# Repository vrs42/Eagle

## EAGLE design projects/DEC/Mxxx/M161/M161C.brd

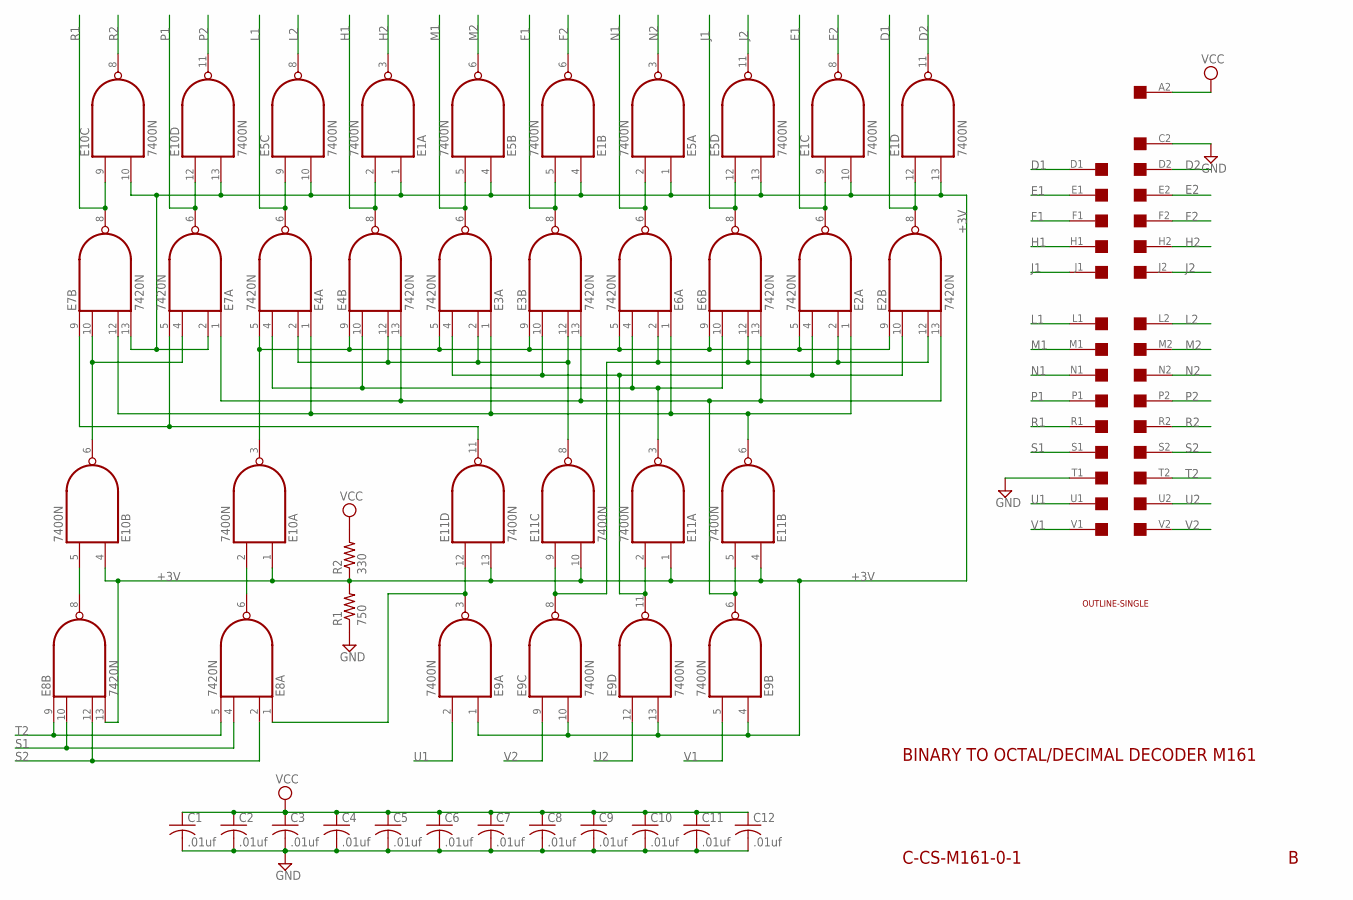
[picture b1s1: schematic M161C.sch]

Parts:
C1, C2, C3, C4, C5, C6, C7, C8, C9, C10, C11, C12: .01uf; C050-025X075
E1, E5, E9, E10, E11: 7400N; DIL14
E2, E3, E4, E6, E7, E8: 7420N; DIL14
R1: 750; 0207/10
R2: 330; 0207/10
U$1: OUTLINE-SINGLE; SINGLE
U$4: SINGLE; EDGE-CON2

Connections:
+3V: E1.1 (I0), E1.4 (I0), E1.10 (I1), E1.13 (I1), E5.1 (I0), E5.4 (I0), E5.10 (I1), E5.13 (I1), E7.2 (I1), E7.13 (I3), E8.13 (I3), E9.1 (I0), E9.4 (I0), E9.10 (I1), E9.13 (I1), E10.1 (I0), E10.4 (I0), E10.10 (I1), E10.13 (I1), E11.1 (I0), E11.4 (I0), E11.10 (I1), E11.13 (I1), R1.2, R2.1
D1: E1.12 (I0), E2.8 (O), U$4.D1
D2: E1.11 (O), U$4.D2
E1: E1.9 (I0), E2.6 (O), U$4.E1
E2: E1.8 (O), U$4.E2
F1: E1.5 (I1), E3.8 (O), U$4.F1
F2: E1.6 (O), U$4.F2
GND: C1.2, C2.2, C3.2, C4.2, C5.2, C6.2, C7.2, C8.2, C9.2, C10.2, C11.2, C12.2, E1.7 (GND), E2.7 (GND), E3.7 (GND), E4.7 (GND), E5.7 (GND), E6.7 (GND), E7.7 (GND), E8.7 (GND), E9.7 (GND), E10.7 (GND), E11.7 (GND), R1.1, U$4.C2, U$4.T1
H1: E1.2 (I1), E4.8 (O), U$4.H1
H2: E1.3 (O), U$4.H2
J1: E5.12 (I0), E6.8 (O), U$4.J1
J2: E5.11 (O), U$4.J2
L1: E4.6 (O), E5.9 (I0), U$4.L1
L2: E5.8 (O), U$4.L2
M1: E3.6 (O), E5.5 (I1), U$4.M1
M2: E5.6 (O), U$4.M2
N1: E5.2 (I1), E6.6 (O), U$4.N1
N2: E5.3 (O), U$4.N2
unnamed: E8.8 (O), E10.5 (I1)
unnamed: E7.4 (I2), E7.10 (I1), E10.6 (O)
unnamed: E2.5 (I3), E2.9 (I0), E3.5 (I3), E3.9 (I0), E4.5 (I3), E4.9 (I0), E6.5 (I3), E6.9 (I0), E10.3 (O)
unnamed: E8.6 (O), E10.2 (I1)
unnamed: E8.1 (I0), E9.3 (O), E11.12 (I0)
unnamed: E2.2 (I1), E2.12 (I2), E6.2 (I1), E6.12 (I2), E9.8 (O), E11.9 (I0)
unnamed: E2.4 (I2), E2.10 (I1), E3.4 (I2), E3.10 (I1), E9.11 (O), E11.2 (I1)
unnamed: E2.13 (I3), E3.13 (I3), E4.13 (I3), E6.13 (I3), E7.1 (I0), E9.6 (O), E11.5 (I1)
unnamed: E3.2 (I1), E3.12 (I2), E4.2 (I1), E4.12 (I2), E11.8 (O)
unnamed: E7.5 (I3), E7.9 (I0), E11.11 (O)
unnamed: E4.4 (I2), E4.10 (I1), E6.4 (I2), E6.10 (I1), E11.3 (O)
unnamed: E2.1 (I0), E3.1 (I0), E4.1 (I0), E6.1 (I0), E7.12 (I2), E11.6 (O)
P1: E7.6 (O), E10.12 (I0), U$4.P1
P2: E10.11 (O), U$4.P2
R1: E7.8 (O), E10.9 (I0), U$4.R1
R2: E10.8 (O), U$4.R2
S1: E8.4 (I2), E8.10 (I1), U$4.S1
S2: E8.2 (I1), E8.12 (I2), U$4.S2
T2: E8.5 (I3), E8.9 (I0), U$4.T2
U1: E9.2 (I1), U$4.U1
U2: E9.12 (I0), U$4.U2
V1: E9.5 (I1), U$4.V1
V2: E9.9 (I0), U$4.V2
VCC: C1.1, C2.1, C3.1, C4.1, C5.1, C6.1, C7.1, C8.1, C9.1, C10.1, C11.1, C12.1, E1.14 (VCC), E2.14 (VCC), E3.14 (VCC), E4.14 (VCC), E5.14 (VCC), E6.14 (VCC), E7.14 (VCC), E8.14 (VCC), E9.14 (VCC), E10.14 (VCC), E11.14 (VCC), R2.2, U$4.A2

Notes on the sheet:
BINARY TO OCTAL/DECIMAL DECODER M161
C-CS-M161-0-1

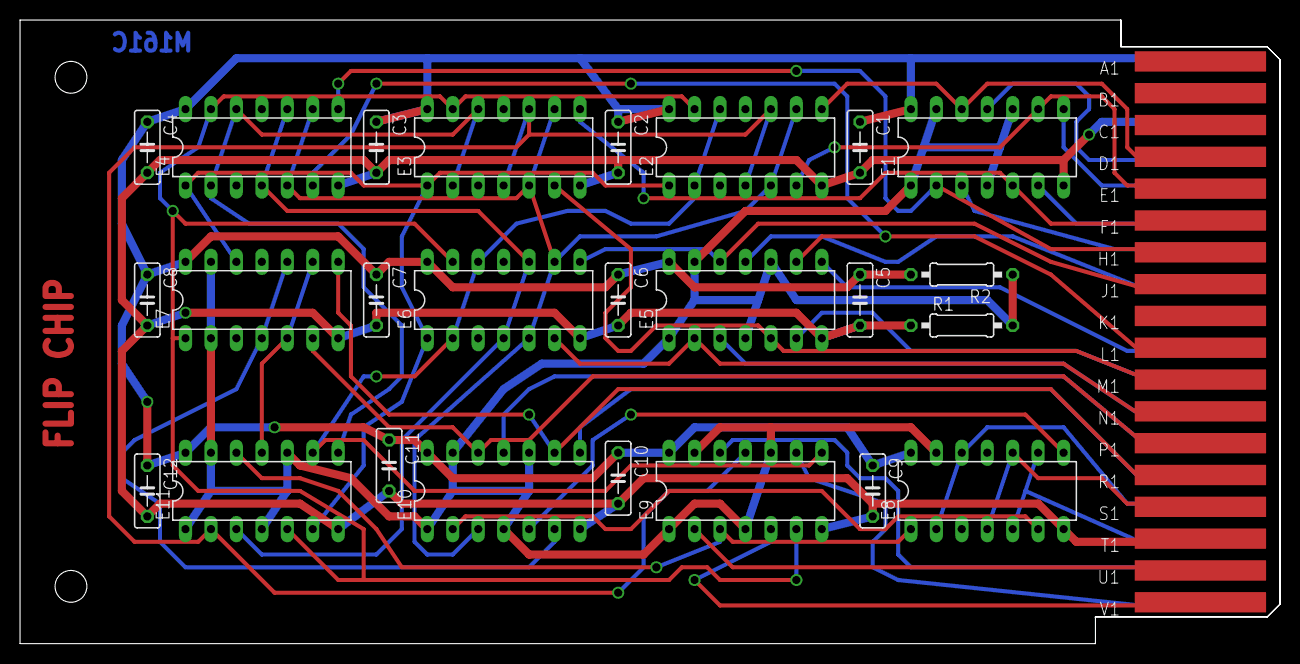
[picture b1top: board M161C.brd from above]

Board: 2 copper layers, 125.7 x 62.2 mm, 28 parts (0 on the bottom side), 42 nets.

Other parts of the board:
U$2: FLIPCHIP

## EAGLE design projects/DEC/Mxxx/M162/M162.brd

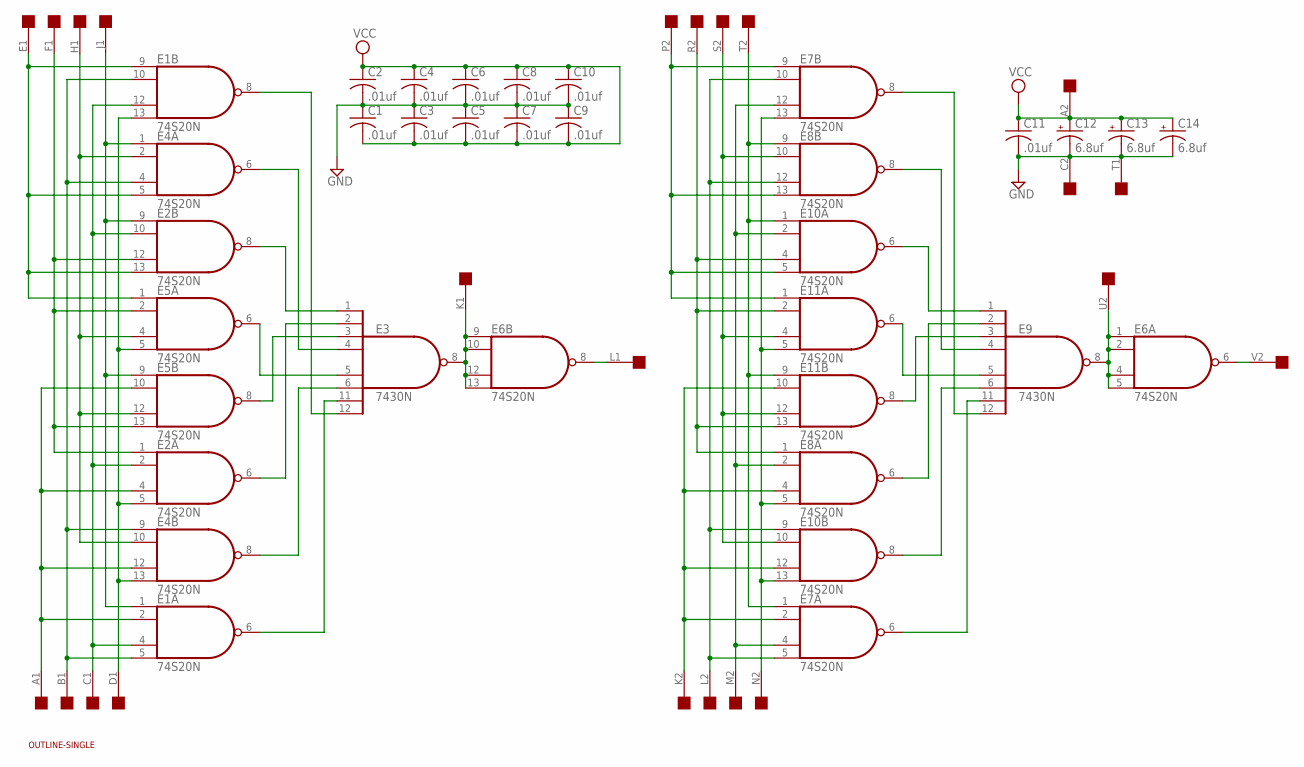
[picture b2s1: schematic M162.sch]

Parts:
C1, C2, C3, C4, C5, C6, C7, C8, C9, C10, C11: .01uf; C050-025X075
C12, C13, C14: 6.8uf; E22-6
E1, E2, E4, E5, E6, E7, E8, E10, E11: 74S20N; DIL14
E3, E9: 7430N; DIL14
U$1: OUTLINE-SINGLE; SINGLE
U$2: EDGE-2CONNECTOR; EDGE-CON2

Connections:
GND: C1.1, C2.2, C3.1, C4.2, C5.1, C6.2, C7.1, C8.2, C9.1, C10.2, C11.2, C12.-, C13.-, C14.-, E1.7 (GND), E2.7 (GND), E3.7 (GND), E4.7 (GND), E5.7 (GND), E6.7 (GND), E7.7 (GND), E8.7 (GND), E9.7 (GND), E10.7 (GND), E11.7 (GND), U$2.C2, U$2.T1
unnamed: E1.2 (I1), E2.4 (I2), E4.12 (I2), E5.10 (I1), U$2.A1
unnamed: E1.13 (I3), E2.5 (I3), E4.13 (I3), E5.5 (I3), U$2.D1
unnamed: E1.1 (I0), E2.9 (I0), E4.1 (I0), E5.9 (I0), U$2.J1
unnamed: E4.2 (I1), E4.10 (I1), E5.4 (I2), E5.12 (I2), U$2.H1
unnamed: E1.4 (I2), E1.12 (I2), E2.2 (I1), E2.10 (I1), U$2.C1
unnamed: E1.5 (I3), E1.10 (I1), E4.4 (I2), E4.9 (I0), U$2.B1
unnamed: E2.1 (I0), E2.12 (I2), E5.2 (I1), E5.13 (I3), U$2.F1
unnamed: E1.9 (I0), E2.13 (I3), E4.5 (I3), E5.1 (I0), U$2.E1
unnamed: E1.8 (O), E3.12 (I7)
unnamed: E3.4 (I3), E4.6 (O)
unnamed: E2.8 (O), E3.1 (I0)
unnamed: E3.5 (I4), E5.6 (O)
unnamed: E3.3 (I2), E5.8 (O)
unnamed: E2.6 (O), E3.2 (I1)
unnamed: E1.6 (O), E3.11 (I6)
unnamed: E3.6 (I5), E4.8 (O)
unnamed: E3.8 (O), E6.9 (I0), E6.10 (I1), E6.12 (I2), E6.13 (I3), U$2.K1
unnamed: E7.2 (I1), E8.4 (I2), E10.12 (I2), E11.10 (I1), U$2.K2
unnamed: E7.13 (I3), E8.5 (I3), E10.13 (I3), E11.5 (I3), U$2.N2
unnamed: E7.1 (I0), E8.9 (I0), E10.1 (I0), E11.9 (I0), U$2.T2
unnamed: E8.10 (I1), E10.10 (I1), E11.4 (I2), E11.12 (I2), U$2.S2
unnamed: E7.4 (I2), E7.12 (I2), E8.2 (I1), E10.2 (I1), U$2.M2
unnamed: E7.5 (I3), E7.10 (I1), E8.12 (I2), E10.9 (I0), U$2.L2
unnamed: E8.1 (I0), E10.4 (I2), E11.2 (I1), E11.13 (I3), U$2.R2
unnamed: E7.9 (I0), E8.13 (I3), E10.5 (I3), E11.1 (I0), U$2.P2
unnamed: E7.8 (O), E9.12 (I7)
unnamed: E8.8 (O), E9.4 (I3)
unnamed: E9.1 (I0), E10.6 (O)
unnamed: E9.5 (I4), E11.6 (O)
unnamed: E9.3 (I2), E11.8 (O)
unnamed: E8.6 (O), E9.2 (I1)
unnamed: E7.6 (O), E9.11 (I6)
unnamed: E9.6 (I5), E10.8 (O)
unnamed: E6.1 (I0), E6.2 (I1), E6.4 (I2), E6.5 (I3), E9.8 (O), U$2.U2
unnamed: E6.6 (O), U$2.V2
unnamed: E6.8 (O), U$2.L1
VCC: C1.2, C2.1, C3.2, C4.1, C5.2, C6.1, C7.2, C8.1, C9.2, C10.1, C11.1, C12.+, C13.+, C14.+, E1.14 (VCC), E2.14 (VCC), E3.14 (VCC), E4.14 (VCC), E5.14 (VCC), E6.14 (VCC), E7.14 (VCC), E8.14 (VCC), E9.14 (VCC), E10.14 (VCC), E11.14 (VCC), U$2.A2

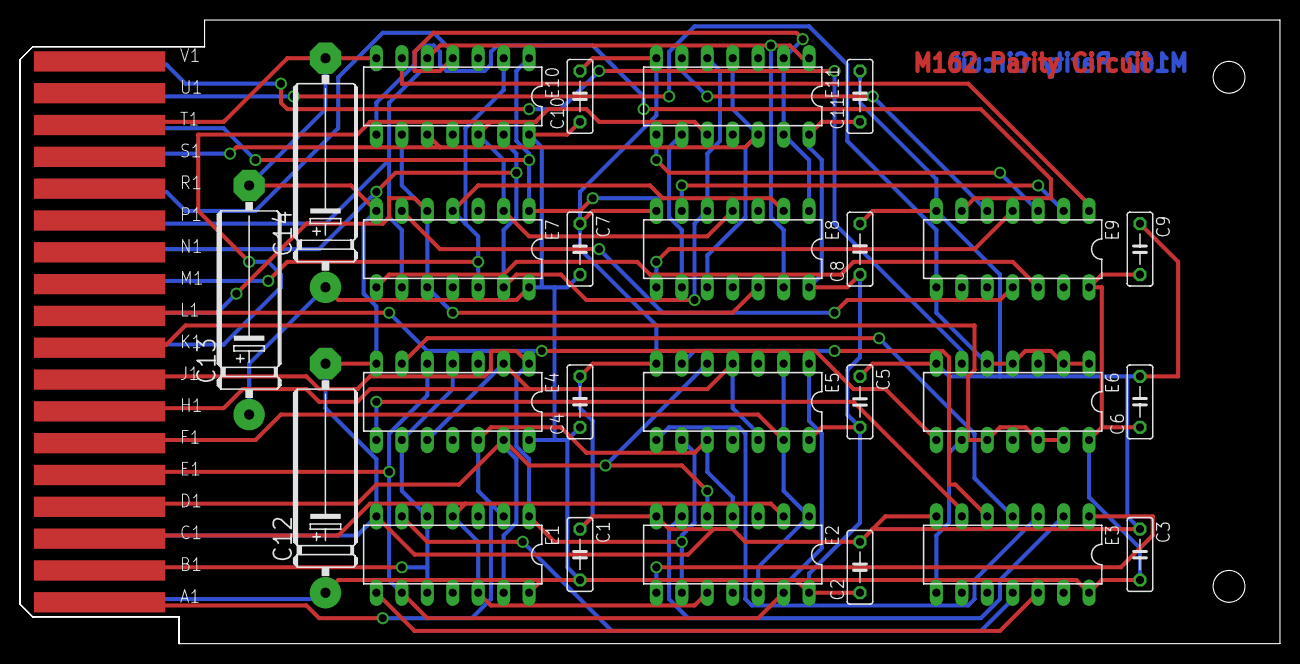
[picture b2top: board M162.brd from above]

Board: 2 copper layers, 125.7 x 62.2 mm, 27 parts (0 on the bottom side), 38 nets.

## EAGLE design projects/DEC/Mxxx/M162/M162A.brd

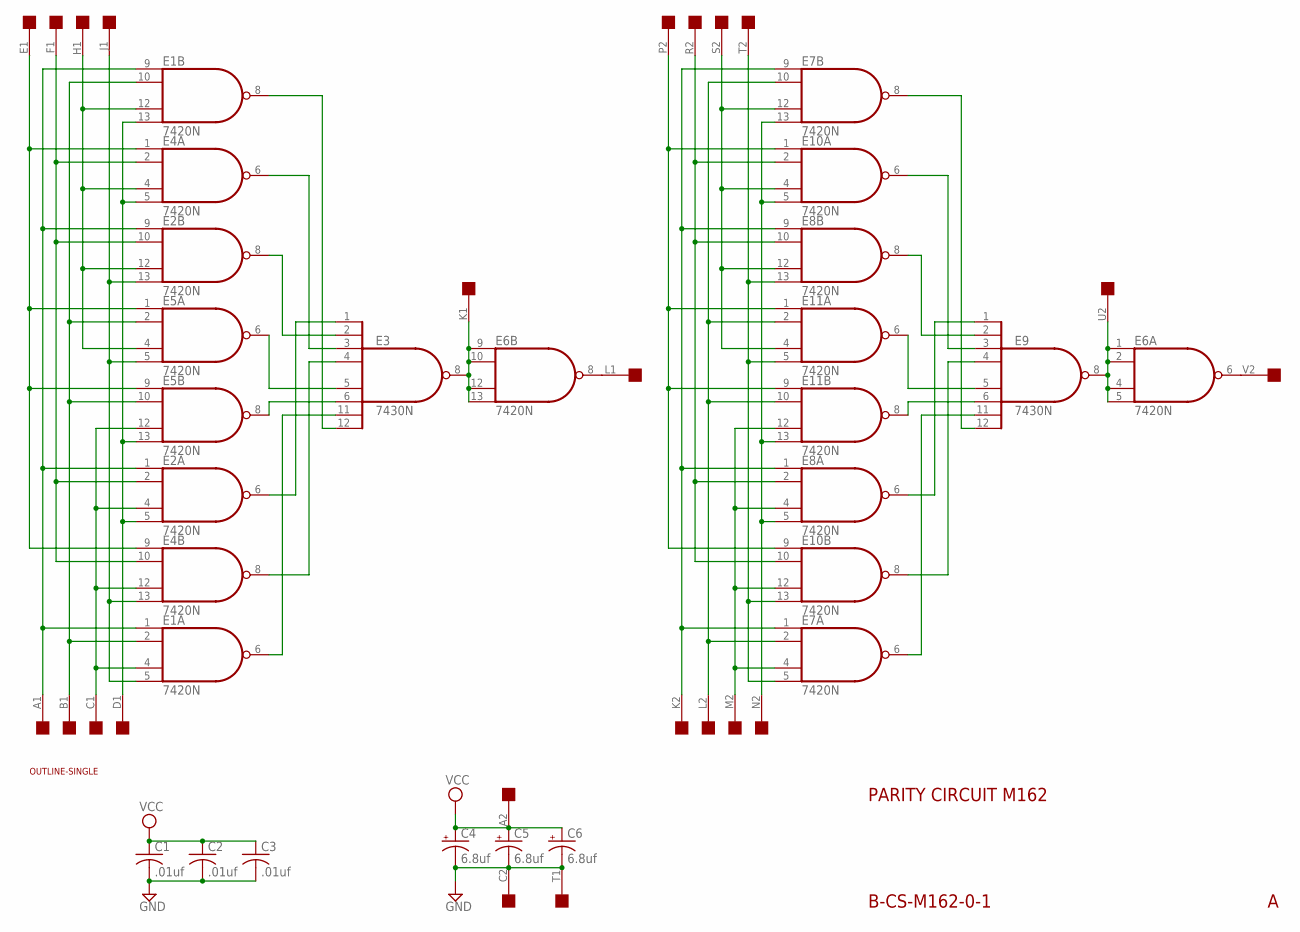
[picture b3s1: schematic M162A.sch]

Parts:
C1, C2, C3: .01uf; C075-032X103
C4, C5, C6: 6.8uf; E15-5
E1, E2, E4, E5, E6, E7, E8, E10, E11: 7420N; DIL14
E3, E9: 7430N; DIL14
U$1: OUTLINE-SINGLE; SINGLE
U$2: EDGE-2CONNECTOR; EDGE-CON2

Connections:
GND: C1.2, C2.2, C3.2, C4.-, C5.-, C6.-, E1.7 (GND), E2.7 (GND), E3.7 (GND), E4.7 (GND), E5.7 (GND), E6.7 (GND), E7.7 (GND), E8.7 (GND), E9.7 (GND), E10.7 (GND), E11.7 (GND), U$2.C2, U$2.T1
unnamed: E1.4 (I2), E2.4 (I2), E4.12 (I2), E5.12 (I2), U$2.C1
unnamed: E1.13 (I3), E2.5 (I3), E4.5 (I3), E5.13 (I3), U$2.D1
unnamed: E3.4 (I3), E4.8 (O)
unnamed: E1.12 (I2), E2.12 (I2), E4.4 (I2), E5.4 (I2), U$2.H1
unnamed: E2.2 (I1), E2.10 (I1), E4.2 (I1), E4.10 (I1), U$2.F1
unnamed: E1.2 (I1), E1.10 (I1), E5.2 (I1), E5.10 (I1), U$2.B1
unnamed: E7.12 (I2), E8.12 (I2), E10.4 (I2), E11.4 (I2), U$2.S2
unnamed: E1.1 (I0), E1.9 (I0), E2.1 (I0), E2.9 (I0), U$2.A1
unnamed: E1.8 (O), E3.12 (I7)
unnamed: E3.3 (I2), E4.6 (O)
unnamed: E7.6 (O), E9.11 (I6)
unnamed: E3.5 (I4), E5.6 (O)
unnamed: E3.6 (I5), E5.8 (O)
unnamed: E2.6 (O), E3.1 (I0)
unnamed: E1.6 (O), E3.11 (I6)
unnamed: E2.8 (O), E3.2 (I1)
unnamed: E3.8 (O), E6.9 (I0), E6.10 (I1), E6.12 (I2), E6.13 (I3), U$2.K1
unnamed: E7.2 (I1), E7.10 (I1), E11.2 (I1), E11.10 (I1), U$2.L2
unnamed: E7.13 (I3), E8.5 (I3), E10.5 (I3), E11.13 (I3), U$2.N2
unnamed: E10.1 (I0), E10.9 (I0), E11.1 (I0), E11.9 (I0), U$2.P2
unnamed: E8.2 (I1), E8.10 (I1), E10.2 (I1), E10.10 (I1), U$2.R2
unnamed: E8.8 (O), E9.2 (I1)
unnamed: E7.5 (I3), E8.13 (I3), E10.13 (I3), E11.5 (I3), U$2.T2
unnamed: E7.8 (O), E9.12 (I7)
unnamed: E9.3 (I2), E10.6 (O)
unnamed: E9.5 (I4), E11.6 (O)
unnamed: E9.6 (I5), E11.8 (O)
unnamed: E9.4 (I3), E10.8 (O)
unnamed: E6.1 (I0), E6.2 (I1), E6.4 (I2), E6.5 (I3), E9.8 (O), U$2.U2
unnamed: E6.6 (O), U$2.V2
unnamed: E6.8 (O), U$2.L1
unnamed: E1.5 (I3), E2.13 (I3), E4.13 (I3), E5.5 (I3), U$2.J1
unnamed: E4.1 (I0), E4.9 (I0), E5.1 (I0), E5.9 (I0), U$2.E1
unnamed: E7.4 (I2), E8.4 (I2), E10.12 (I2), E11.12 (I2), U$2.M2
unnamed: E7.1 (I0), E7.9 (I0), E8.1 (I0), E8.9 (I0), U$2.K2
S$14: E8.6 (O), E9.1 (I0)
VCC: C1.1, C2.1, C3.1, C4.+, C5.+, C6.+, E1.14 (VCC), E2.14 (VCC), E3.14 (VCC), E4.14 (VCC), E5.14 (VCC), E6.14 (VCC), E7.14 (VCC), E8.14 (VCC), E9.14 (VCC), E10.14 (VCC), E11.14 (VCC), U$2.A2

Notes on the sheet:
B-CS-M162-0-1
PARITY CIRCUIT M162

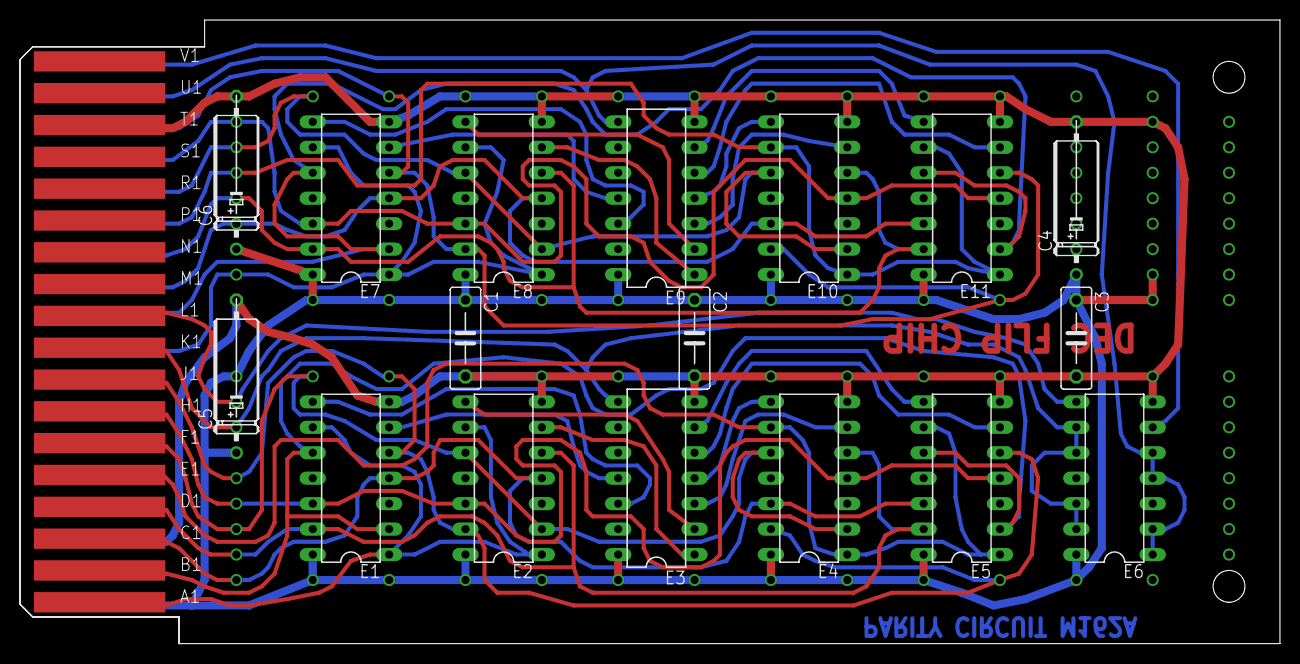
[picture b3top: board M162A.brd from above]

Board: 2 copper layers, 125.7 x 62.2 mm, 19 parts (0 on the bottom side), 38 nets.

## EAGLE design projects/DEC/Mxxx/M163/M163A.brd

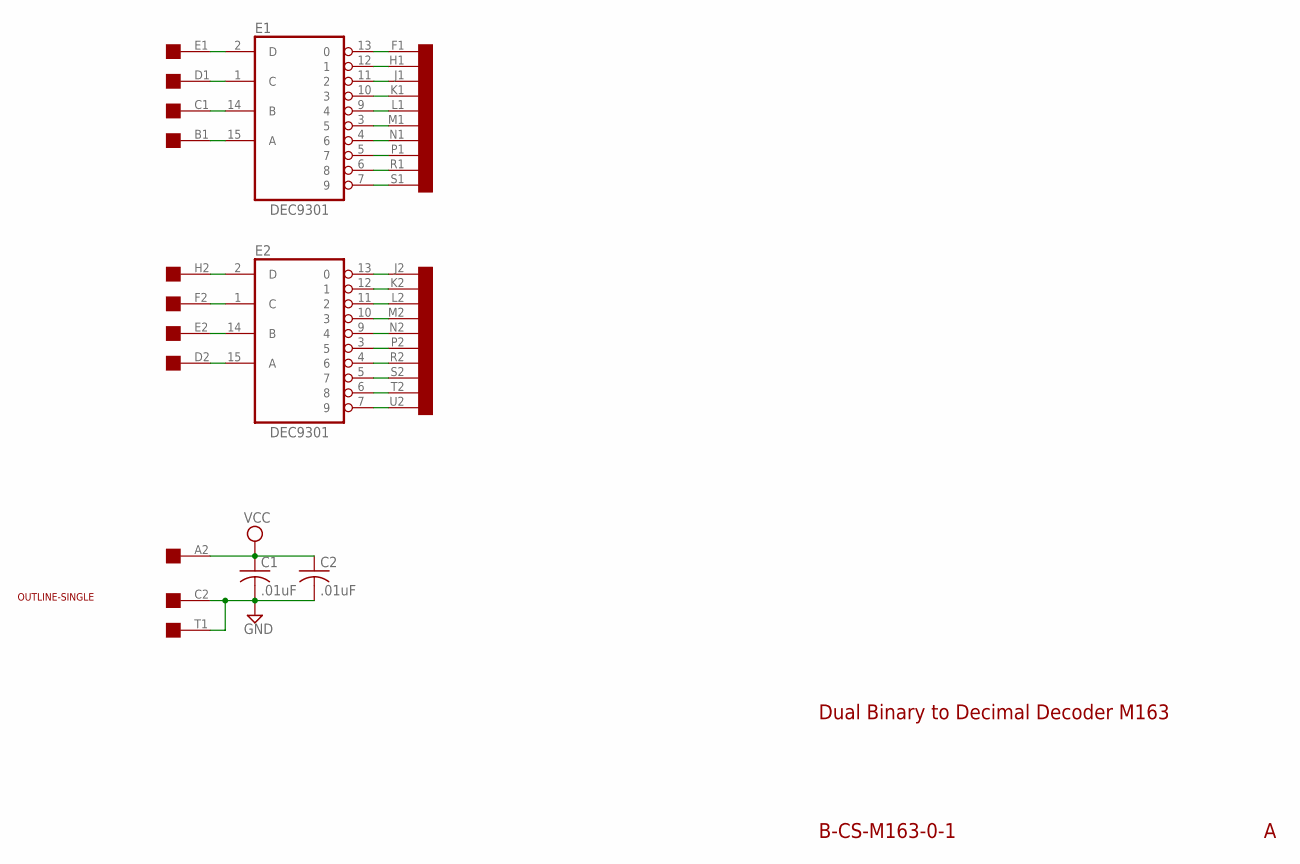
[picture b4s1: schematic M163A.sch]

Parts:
C1, C2: .01uF; C050-025X075
E1, E2: DEC9301; DIL16
U$1: OUTLINE-SINGLE; SINGLE
U$2: SINGLE; EDGE-CON2

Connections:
GND: C1.2, C2.2, E1.8 (GND), E2.8 (GND), U$2.C2, U$2.T1
unnamed: E1.15 (A), U$2.B1
unnamed: E1.14 (B), U$2.C1
unnamed: E1.1 (C), U$2.D1
unnamed: E1.2 (D), U$2.E1
unnamed: E1.13 (0), U$2.F1
unnamed: E1.12 (1), U$2.H1
unnamed: E1.11 (2), U$2.J1
unnamed: E1.10 (3), U$2.K1
unnamed: E1.3 (5), U$2.M1
unnamed: E1.9 (4), U$2.L1
unnamed: E1.4 (6), U$2.N1
unnamed: E1.5 (7), U$2.P1
unnamed: E1.6 (8), U$2.R1
unnamed: E1.7 (9), U$2.S1
unnamed: E2.2 (D), U$2.H2
unnamed: E2.1 (C), U$2.F2
unnamed: E2.15 (A), U$2.D2
unnamed: E2.14 (B), U$2.E2
unnamed: E2.11 (2), U$2.L2
unnamed: E2.10 (3), U$2.M2
unnamed: E2.9 (4), U$2.N2
unnamed: E2.3 (5), U$2.P2
unnamed: E2.4 (6), U$2.R2
unnamed: E2.5 (7), U$2.S2
unnamed: E2.6 (8), U$2.T2
unnamed: E2.12 (1), U$2.K2
unnamed: E2.13 (0), U$2.J2
unnamed: E2.7 (9), U$2.U2
VCC: C1.1, C2.1, E1.16 (VCC), E2.16 (VCC), U$2.A2

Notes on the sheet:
B-CS-M163-0-1
Dual Binary to Decimal Decoder M163

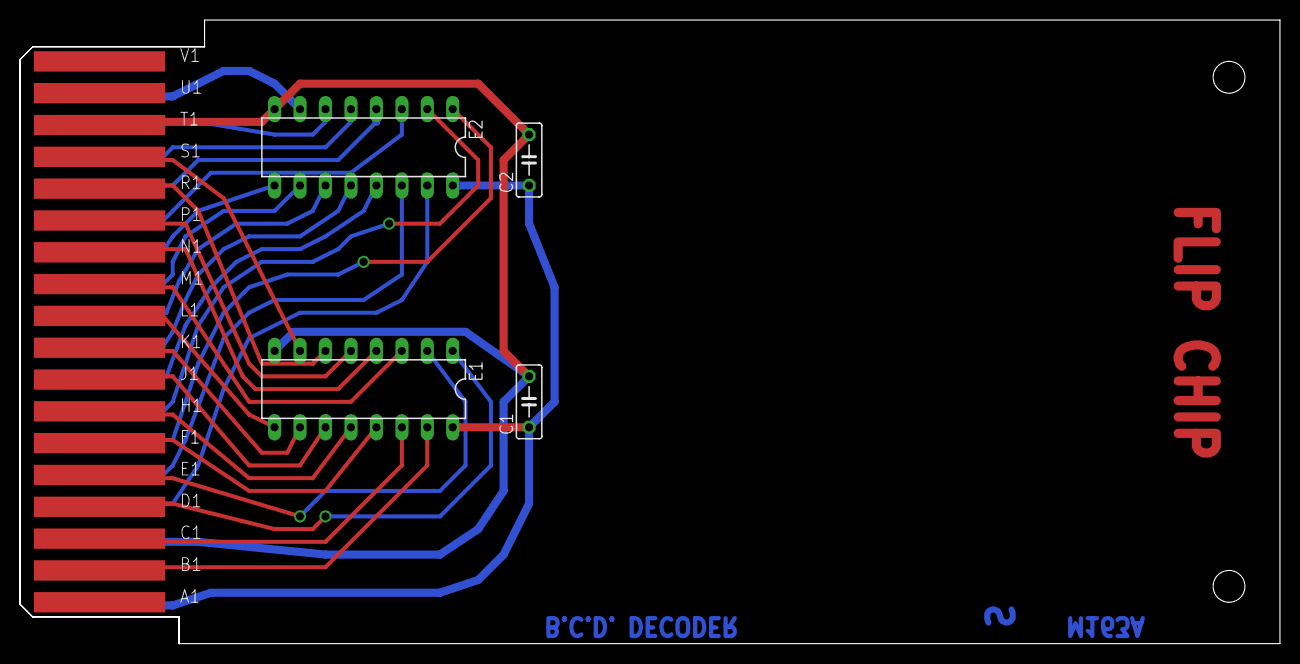
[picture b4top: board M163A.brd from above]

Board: 2 copper layers, 125.7 x 62.2 mm, 6 parts (0 on the bottom side), 30 nets.
